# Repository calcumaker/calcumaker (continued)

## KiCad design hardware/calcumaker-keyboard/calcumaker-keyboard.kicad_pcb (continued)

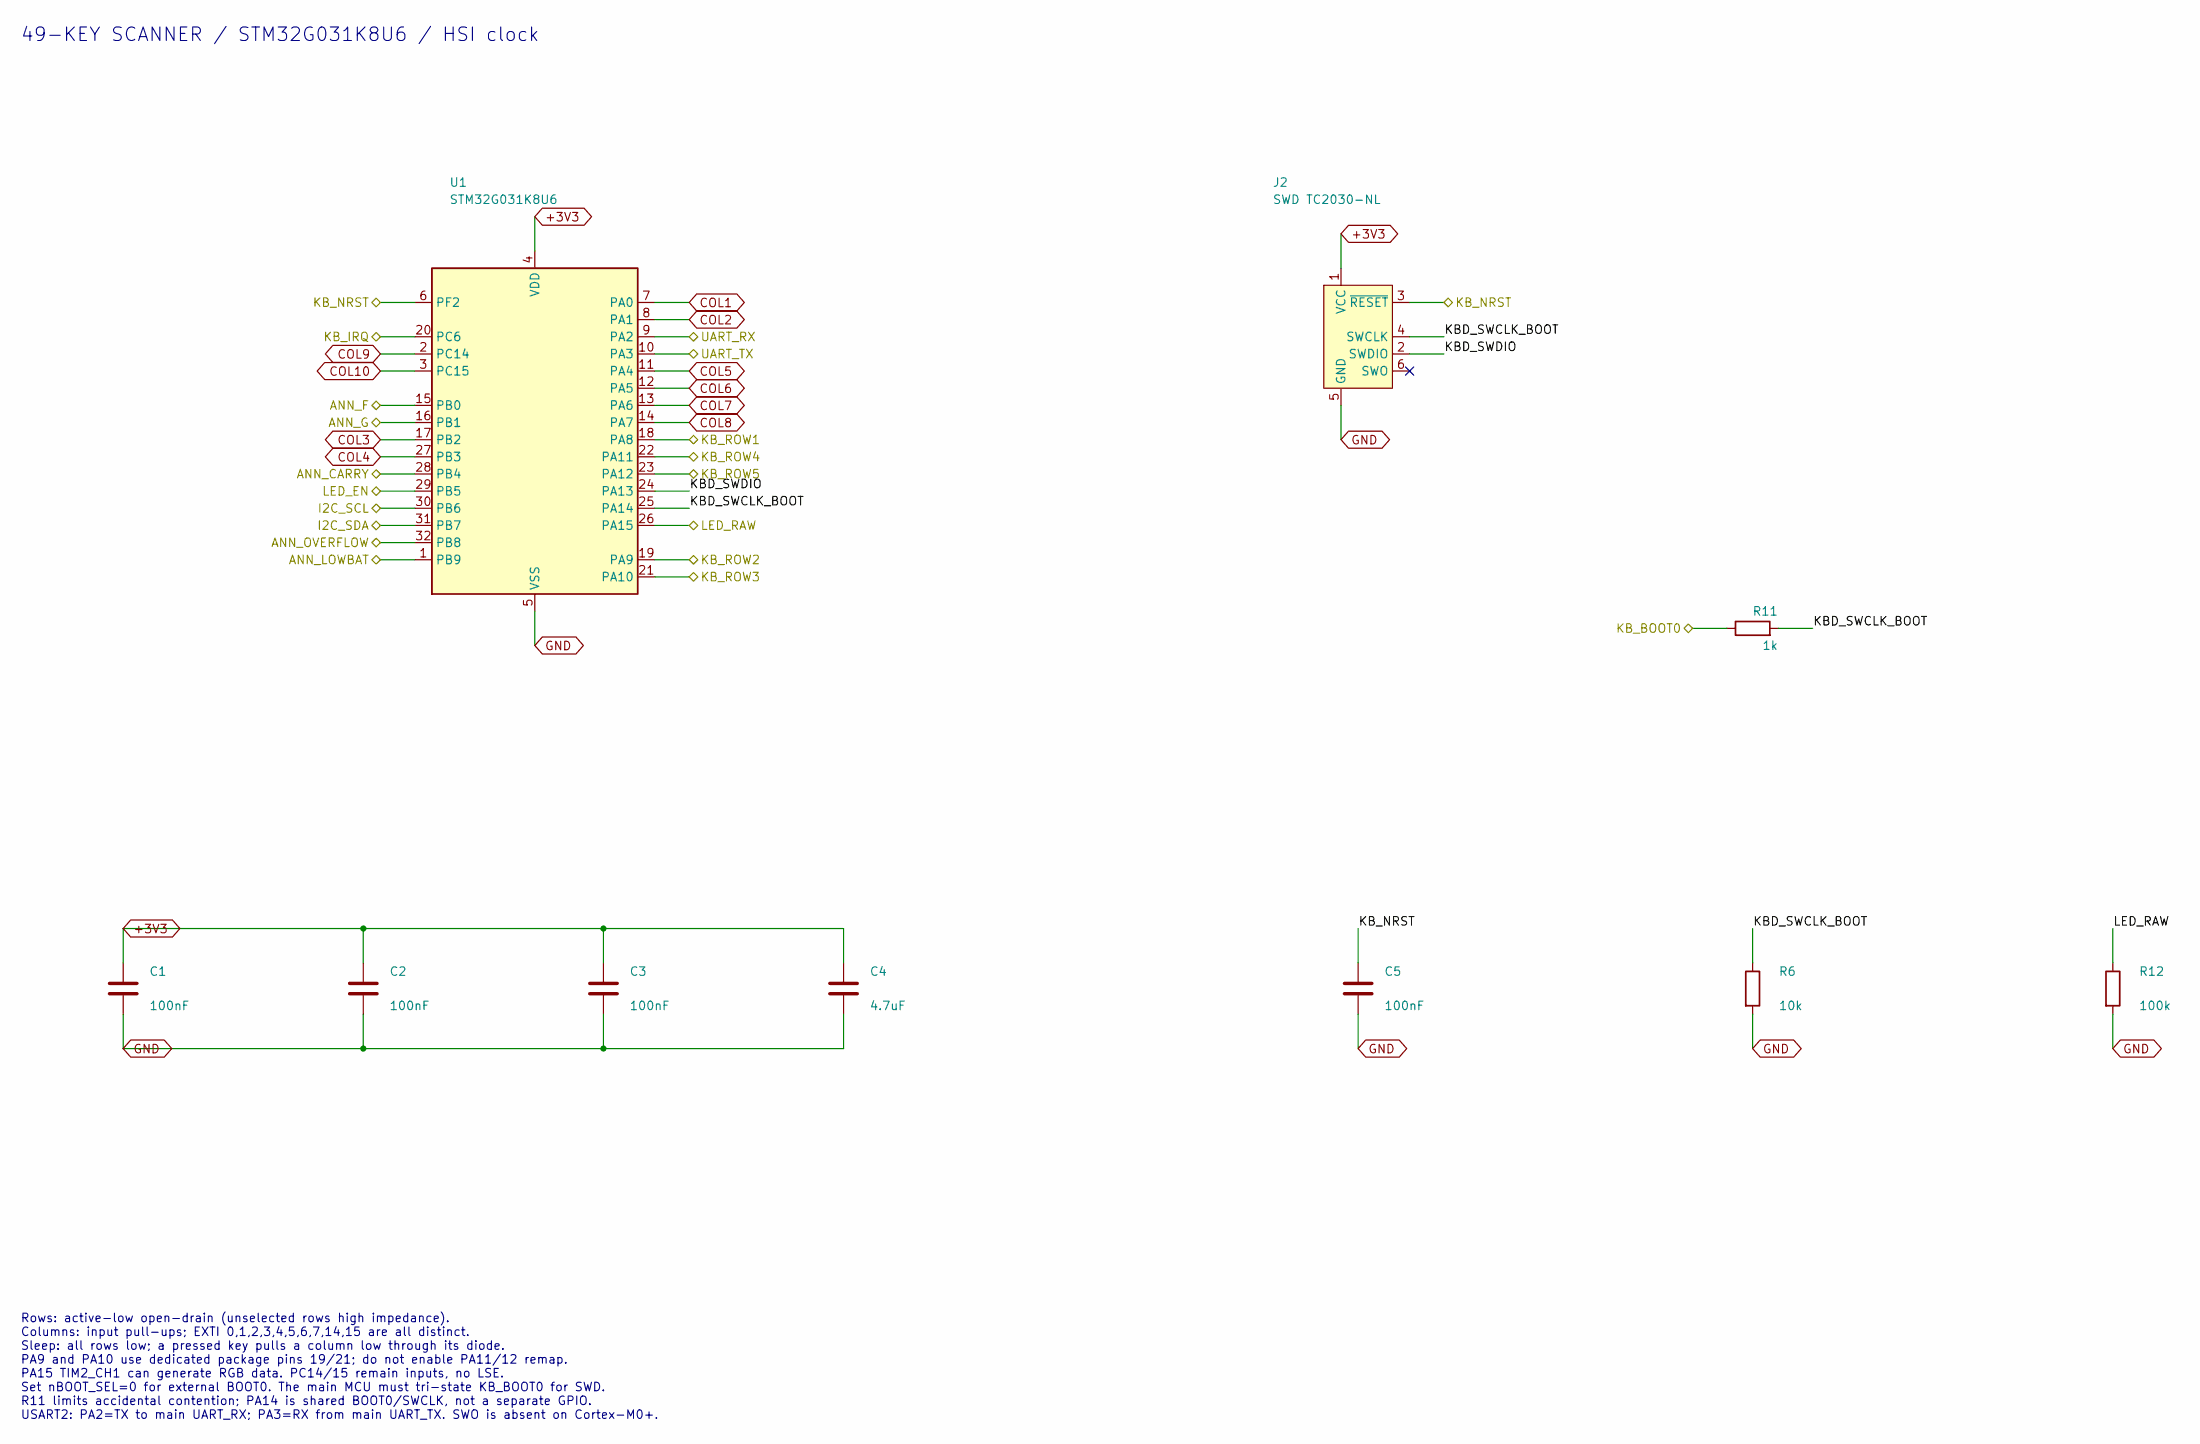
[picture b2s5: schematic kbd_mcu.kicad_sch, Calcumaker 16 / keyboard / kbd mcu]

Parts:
C1, C2, C3, C5: 100nF; C_0402_1005Metric; LCSC C1525
C4: 4.7uF; C_0603_1608Metric
J2: SWD TC2030-NL; Tag-Connect_TC2030-IDC-NL_2x03_P1.27mm_Vertical
R6: 10k; R_0402_1005Metric; LCSC C25744
R11: 1k; R_0402_1005Metric
R12: 100k; R_0402_1005Metric
U1: STM32G031K8U6; UFQFPN-32-1EP_5x5mm_P0.5mm_EP3.5x3.5mm; MPN STM32G031K8U6; LCSC C432207

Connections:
+3V3: C1.1, C2.1, C3.1, C4.1, J2.1 (VCC), U1.4 (VDD); also elsewhere on the board
/ANN_CARRY: U1.28 (PB4); also elsewhere on the board
/ANN_F: U1.15 (PB0); also elsewhere on the board
/ANN_G: U1.16 (PB1); also elsewhere on the board
/ANN_LOWBAT: U1.1 (PB9); also elsewhere on the board
/ANN_OVERFLOW: U1.32 (PB8); also elsewhere on the board
/I2C_SCL: U1.30 (PB6); also elsewhere on the board
/I2C_SDA: U1.31 (PB7); also elsewhere on the board
/KB_BOOT0: R11.1; also elsewhere on the board
/KB_IRQ: U1.20 (PC6); also elsewhere on the board
/KB_NRST: C5.1, J2.3 (~RESET), U1.6 (PF2); also elsewhere on the board
/KB_ROW1: U1.18 (PA8); also elsewhere on the board
/KB_ROW2: U1.19 (PA9); also elsewhere on the board
/KB_ROW3: U1.21 (PA10); also elsewhere on the board
/KB_ROW4: U1.22 (PA11); also elsewhere on the board
/KB_ROW5: U1.23 (PA12); also elsewhere on the board
/KbdMCU/KBD_SWCLK_BOOT: J2.4 (SWCLK), R6.1, R11.2, U1.25 (PA14)
/KbdMCU/KBD_SWDIO: J2.2 (SWDIO), U1.24 (PA13)
/LED_EN: U1.29 (PB5); also elsewhere on the board
/LED_RAW: R12.1, U1.26 (PA15); also elsewhere on the board
/UART_RX: U1.9 (PA2); also elsewhere on the board
/UART_TX: U1.10 (PA3); also elsewhere on the board
COL1: U1.7 (PA0); also elsewhere on the board
COL2: U1.8 (PA1); also elsewhere on the board
COL3: U1.17 (PB2); also elsewhere on the board
COL4: U1.27 (PB3); also elsewhere on the board
COL5: U1.11 (PA4); also elsewhere on the board
COL6: U1.12 (PA5); also elsewhere on the board
COL7: U1.13 (PA6); also elsewhere on the board
COL8: U1.14 (PA7); also elsewhere on the board
COL9: U1.2 (PC14); also elsewhere on the board
COL10: U1.3 (PC15); also elsewhere on the board
GND: C1.2, C2.2, C3.2, C4.2, C5.2, J2.5 (GND), R6.2, R12.2, U1.5 (VSS), U1.33 (VSS); also elsewhere on the board

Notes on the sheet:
49-KEY SCANNER / STM32G031K8U6 / HSI clock
Rows: active-low open-drain (unselected rows high impedance). Columns: input pull-ups; EXTI 0,1,2,3,4,5,6,7,14,15 are all distinct. Sleep: all rows low; a pressed key pulls a column low through its diode. PA9 and PA10 use dedicated package pins 19/21; do not enable PA11/12 remap. PA15 TIM2_CH1 can 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

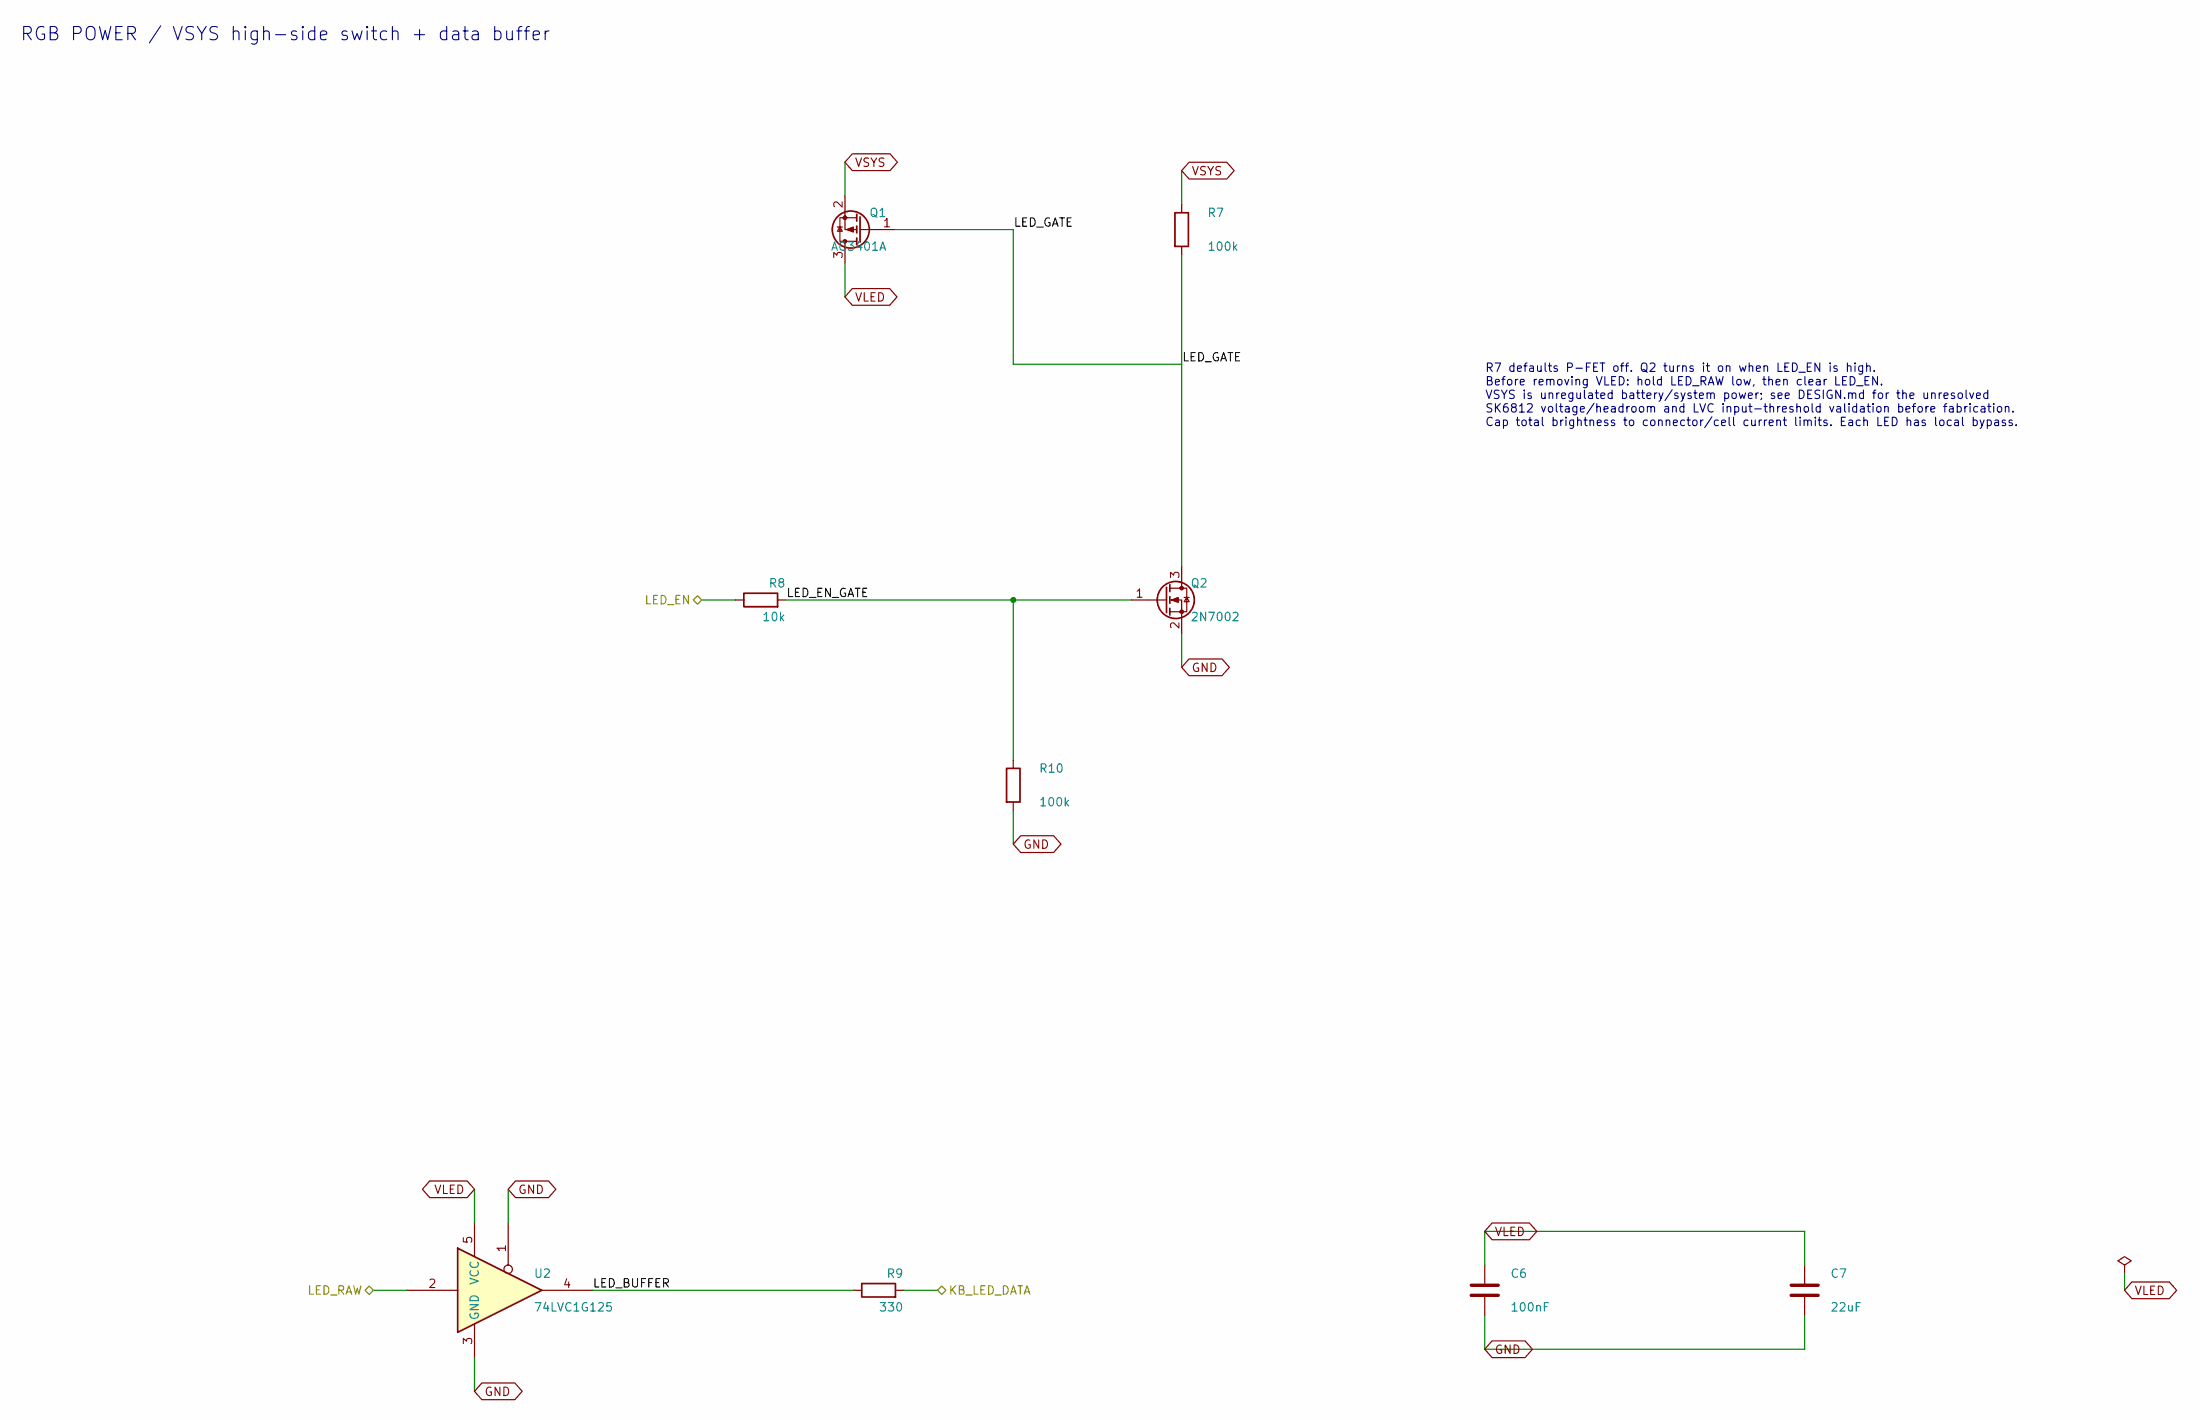
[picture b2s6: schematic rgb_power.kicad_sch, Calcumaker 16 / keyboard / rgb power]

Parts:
C6: 100nF; C_0402_1005Metric; LCSC C1525
C7: 22uF; C_0603_1608Metric
Q1: AO3401A; SOT-23; MPN AO3401A; LCSC C15127
Q2: 2N7002; SOT-23; MPN 2N7002; LCSC C8545
R7, R10: 100k; R_0402_1005Metric; LCSC C25741
R8: 10k; R_0402_1005Metric; LCSC C25744
R9: 330; R_0402_1005Metric
U2: 74LVC1G125; SOT-23-5; MPN SN74LVC1G125DBVR; LCSC C23654

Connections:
/LED_EN: R8.1; also elsewhere on the board
/LED_RAW: U2.2; also elsewhere on the board
/RGBPower/LED_BUFFER: R9.1, U2.4
/RGBPower/LED_EN_GATE: Q2.1 (G), R8.2, R10.1
/RGBPower/LED_GATE: Q1.1 (G), Q2.3 (D), R7.2
/RGB_FIRST: R9.2; also elsewhere on the board
GND: C6.2, C7.2, Q2.2 (S), R10.2, U2.1, U2.3 (GND); also elsewhere on the board
VLED: C6.1, C7.1, Q1.3 (D), U2.5 (VCC); also elsewhere on the board
VSYS: Q1.2 (S), R7.1; also elsewhere on the board

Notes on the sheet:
RGB POWER / VSYS high-side switch + data buffer
R7 defaults P-FET off. Q2 turns it on when LED_EN is high. Before removing VLED: hold LED_RAW low, then clear LED_EN. VSYS is unregulated battery/system power; see DESIGN.md for the unresolved SK6812 voltage/headroom and LVC input-threshold validation before fabrication. Cap total brightness to con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

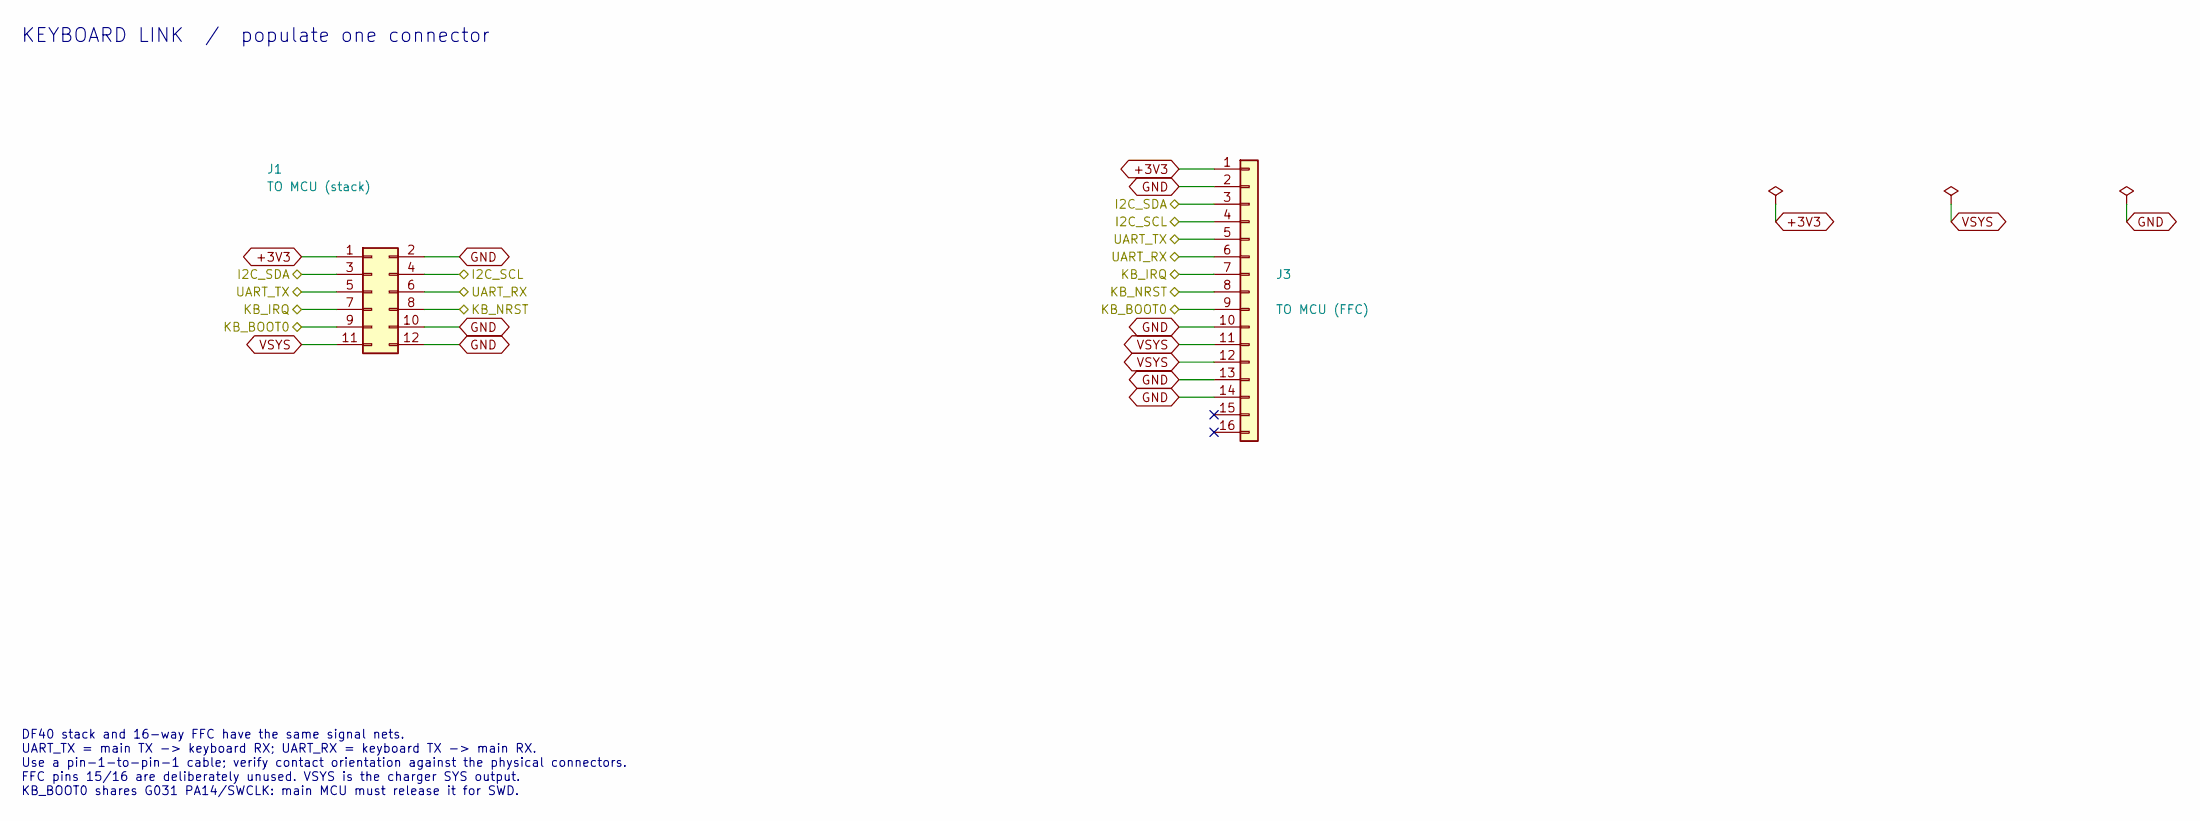
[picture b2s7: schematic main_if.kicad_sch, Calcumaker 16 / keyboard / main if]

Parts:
J1: TO MCU (stack); Hirose_DF40C-12DP-0.4V_2x06-1MP_P0.4mm; MPN DF40C-12DP-0.4V(51); LCSC C6224952
J3: TO MCU (FFC); Hirose_FH12-16S-0.5SH_1x16-1MP_P0.50mm_Horizontal; MPN AFC01-S16FCA-00; LCSC C262665

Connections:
+3V3: J1.1, J3.1; also elsewhere on the board
/I2C_SCL: J1.4, J3.4; also elsewhere on the board
/I2C_SDA: J1.3, J3.3; also elsewhere on the board
/KB_BOOT0: J1.9, J3.9; also elsewhere on the board
/KB_IRQ: J1.7, J3.7; also elsewhere on the board
/KB_NRST: J1.8, J3.8; also elsewhere on the board
/UART_RX: J1.6, J3.6; also elsewhere on the board
/UART_TX: J1.5, J3.5; also elsewhere on the board
GND: J1.2, J1.10, J1.12, J3.2, J3.10, J3.13, J3.14; also elsewhere on the board
VSYS: J1.11, J3.11, J3.12; also elsewhere on the board

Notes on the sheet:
KEYBOARD LINK / populate one connector
DF40 stack and 16-way FFC have the same signal nets. UART_TX = main TX -> keyboard RX; UART_RX = keyboard TX -> main RX. Use a pin-1-to-pin-1 cable; verify contact orientation against the physical connectors. FFC pins 15/16 are deliberately unused. VSYS is the charger SYS output. KB_BOOT0 shares G0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

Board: 2 copper layers, 227 parts (222 on the bottom side), 141 nets, no tracks yet.

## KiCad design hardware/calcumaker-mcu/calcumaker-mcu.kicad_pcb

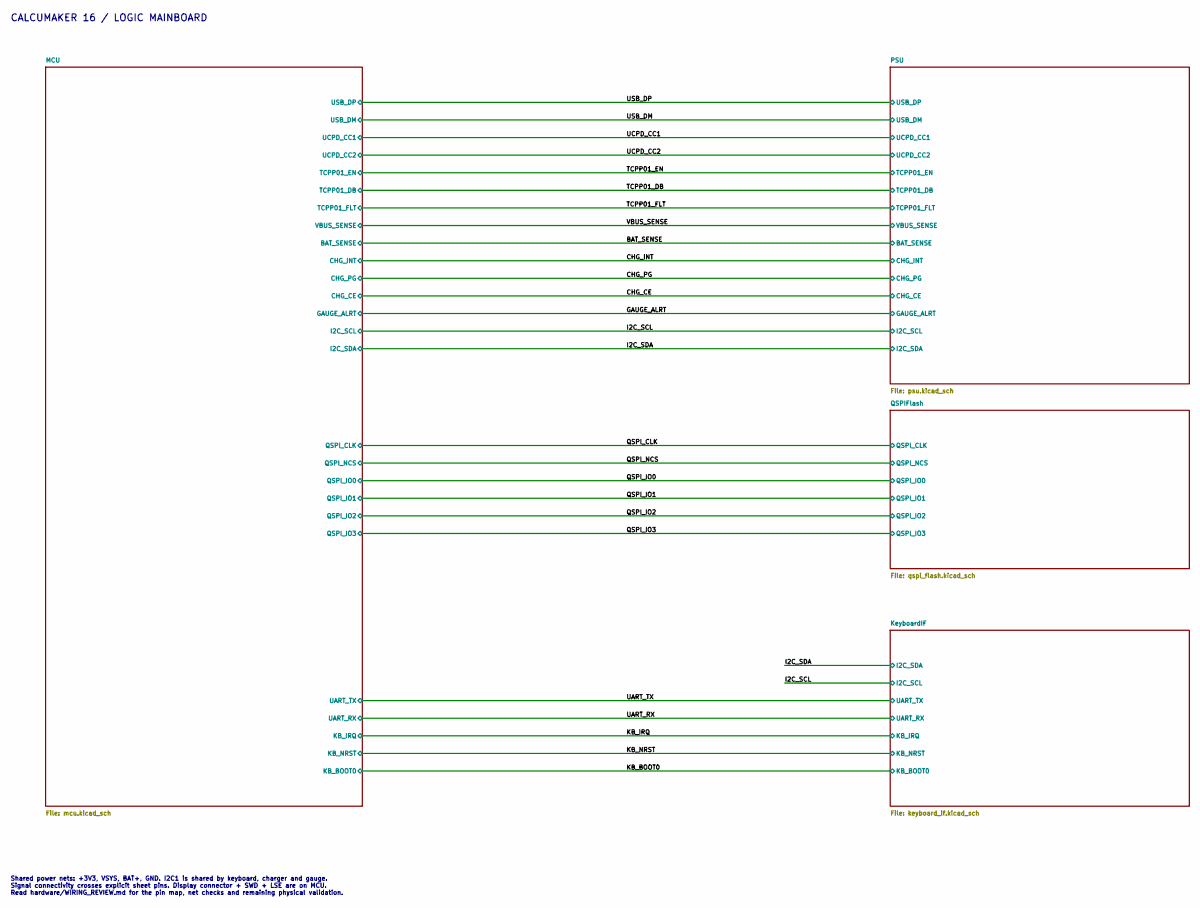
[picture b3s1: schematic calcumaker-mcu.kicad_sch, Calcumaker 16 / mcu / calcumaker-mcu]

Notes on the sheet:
CALCUMAKER 16 / LOGIC MAINBOARD
Shared power nets: +3V3, VSYS, BAT+, GND. I2C1 is shared by keyboard, charger and gauge. Signal connectivity crosses explicit sheet pins. Display connector + SWD + LSE are on MCU. Read hardware/WIRING_REVIEW.md for the pin map, net checks and remaining physical validation.

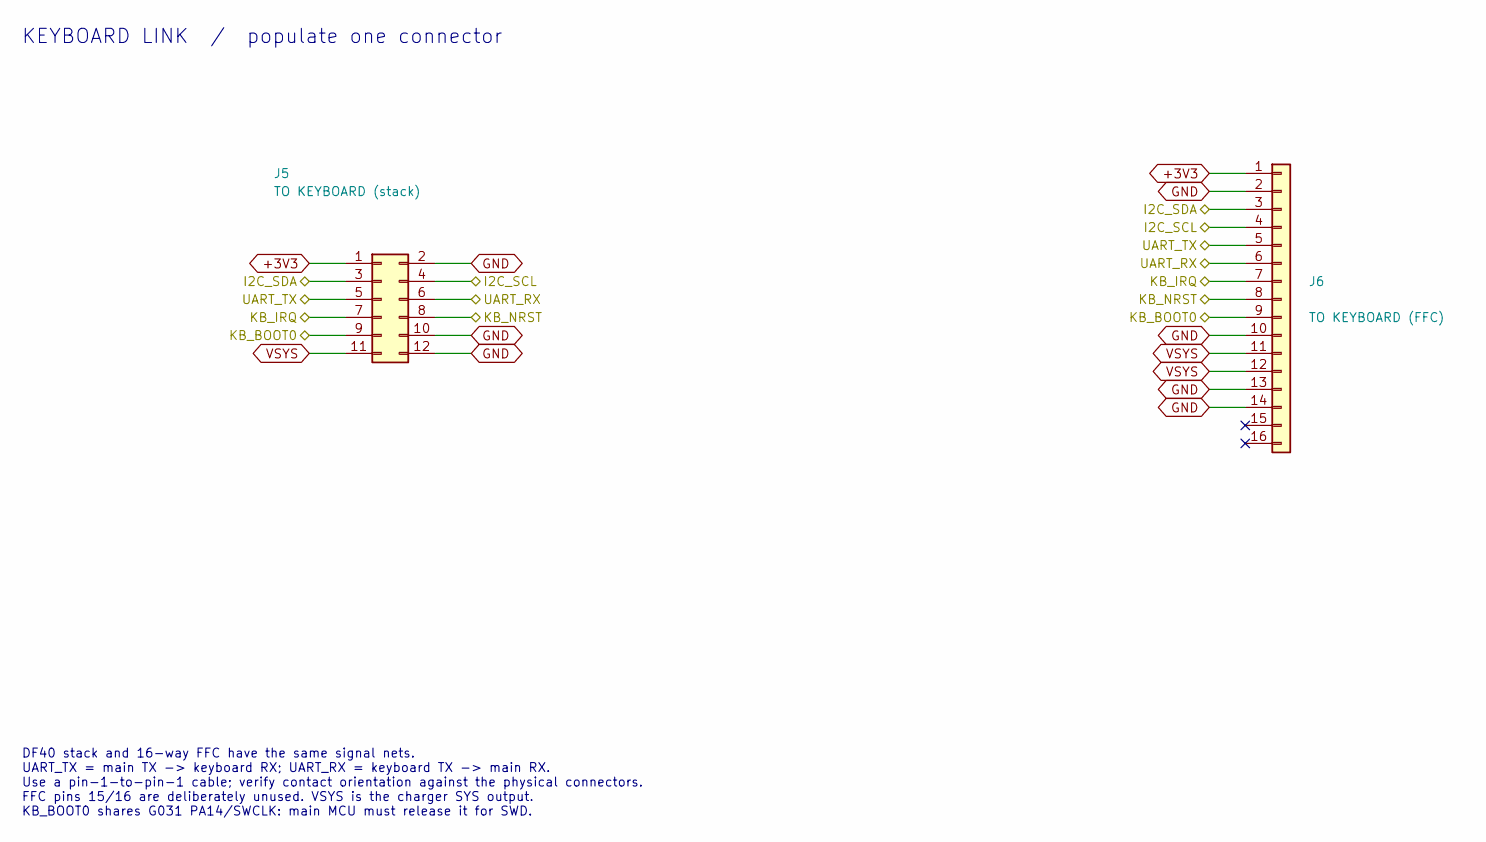
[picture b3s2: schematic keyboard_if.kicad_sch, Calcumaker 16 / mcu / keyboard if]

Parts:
J5: TO KEYBOARD (stack); Hirose_DF40B-12DS-0.4V_2x06-1MP_P0.4mm; MPN DF40B-12DS-0.4V(58); LCSC C3641147
J6: TO KEYBOARD (FFC); Hirose_FH12-16S-0.5SH_1x16-1MP_P0.50mm_Horizontal; MPN AFC01-S16FCA-00; LCSC C262665

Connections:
+3V3: J5.1, J6.1; also elsewhere on the board
/I2C_SCL: J5.4, J6.4; also elsewhere on the board
/I2C_SDA: J5.3, J6.3; also elsewhere on the board
/KB_BOOT0: J5.9, J6.9; also elsewhere on the board
/KB_IRQ: J5.7, J6.7; also elsewhere on the board
/KB_NRST: J5.8, J6.8; also elsewhere on the board
/UART_RX: J5.6, J6.6; also elsewhere on the board
/UART_TX: J5.5, J6.5; also elsewhere on the board
GND: J5.2, J5.10, J5.12, J6.2, J6.10, J6.13, J6.14; also elsewhere on the board
VSYS: J5.11, J6.11, J6.12; also elsewhere on the board

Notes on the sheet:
KEYBOARD LINK / populate one connector
DF40 stack and 16-way FFC have the same signal nets. UART_TX = main TX -> keyboard RX; UART_RX = keyboard TX -> main RX. Use a pin-1-to-pin-1 cable; verify contact orientation against the physical connectors. FFC pins 15/16 are deliberately unused. VSYS is the charger SYS output. KB_BOOT0 shares G0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

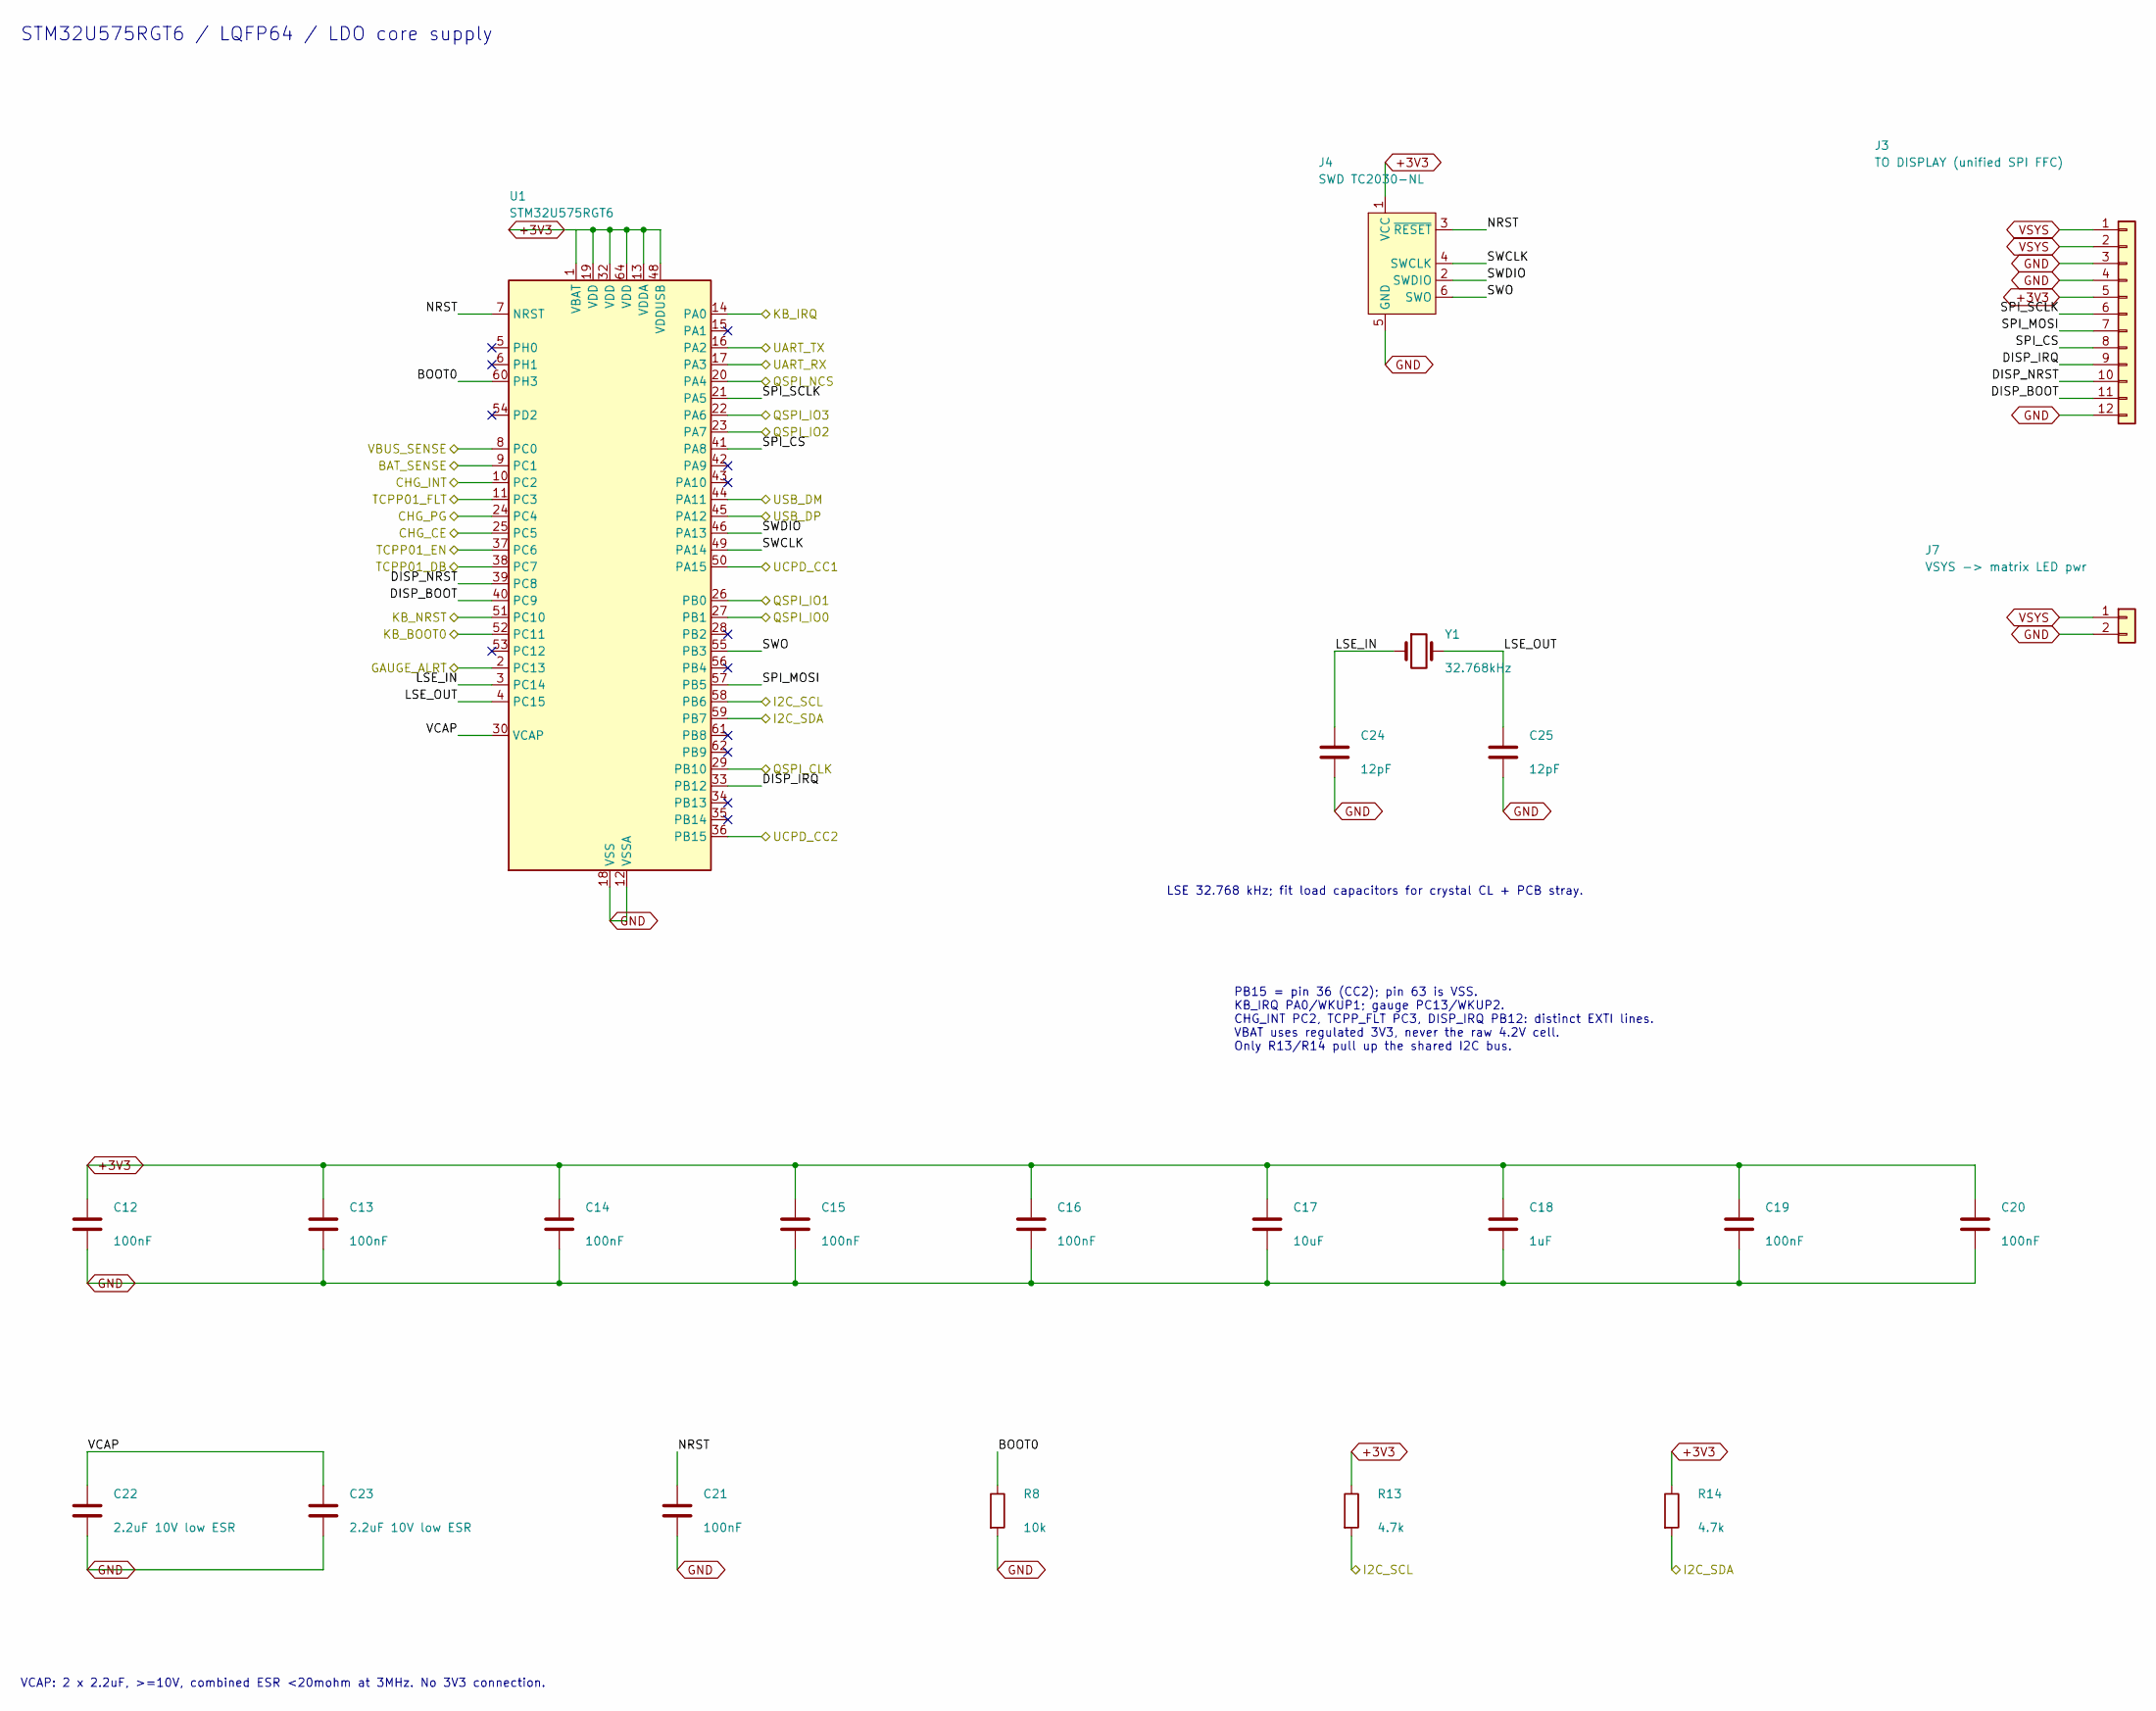
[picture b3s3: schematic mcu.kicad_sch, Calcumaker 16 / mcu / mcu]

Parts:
C12, C13, C14, C15, C16, C19, C20, C21: 100nF; C_0402_1005Metric; LCSC C1525
C17: 10uF; C_0603_1608Metric
C18: 1uF; C_0402_1005Metric; LCSC C29266
C22, C23: 2.2uF 10V low ESR; C_0603_1608Metric
C24, C25: 12pF; C_0402_1005Metric; LCSC C1547
J3: TO DISPLAY (unified SPI FFC); Hirose_FH12-12S-0.5SH_1x12-1MP_P0.50mm_Horizontal; MPN AFC01-S12FCA-00; LCSC C262661
J4: SWD TC2030-NL; Tag-Connect_TC2030-IDC-NL_2x03_P1.27mm_Vertical
J7: VSYS -> matrix LED pwr; JST_PH_S2B-PH-K_1x02_P2.00mm_Horizontal; MPN S2B-PH-K-S; LCSC C173752
R8: 10k; R_0402_1005Metric; LCSC C25744
R13, R14: 4.7k; R_0402_1005Metric
U1: STM32U575RGT6; LQFP-64_10x10mm_P0.5mm; MPN STM32U575RGT6; LCSC C5270980
Y1: 32.768kHz; Crystal_SMD_3215-2Pin_3.2x1.5mm; MPN Q13FC13500004; LCSC C32346

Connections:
+3V3: C12.1, C13.1, C14.1, C15.1, C16.1, C17.1, C18.1, C19.1, C20.1, J3.5, J4.1 (VCC), R13.1, R14.1, U1.1 (VBAT), U1.13 (VDDA), U1.19 (VDD), U1.32 (VDD), U1.48 (VDDUSB), U1.64 (VDD); also elsewhere on the board
/BAT_SENSE: U1.9 (PC1); also elsewhere on the board
/CHG_CE: U1.25 (PC5); also elsewhere on the board
/CHG_INT: U1.10 (PC2); also elsewhere on the board
/CHG_PG: U1.24 (PC4); also elsewhere on the board
/GAUGE_ALRT: U1.2 (PC13); also elsewhere on the board
/I2C_SCL: R13.2, U1.58 (PB6); also elsewhere on the board
/I2C_SDA: R14.2, U1.59 (PB7); also elsewhere on the board
/KB_BOOT0: U1.52 (PC11); also elsewhere on the board
/KB_IRQ: U1.14 (PA0); also elsewhere on the board
/KB_NRST: U1.51 (PC10); also elsewhere on the board
/MCU/BOOT0: R8.1, U1.60 (PH3)
/MCU/DISP_BOOT: J3.11, U1.40 (PC9)
/MCU/DISP_IRQ: J3.9, U1.33 (PB12)
/MCU/DISP_NRST: J3.10, U1.39 (PC8)
/MCU/LSE_IN: C24.1, U1.3 (PC14), Y1.1
/MCU/LSE_OUT: C25.1, U1.4 (PC15), Y1.2
/MCU/NRST: C21.1, J4.3 (~RESET), U1.7 (NRST)
/MCU/SPI_CS: J3.8, U1.41 (PA8)
/MCU/SPI_MOSI: J3.7, U1.57 (PB5)
/MCU/SPI_SCLK: J3.6, U1.21 (PA5)
/MCU/SWCLK: J4.4 (SWCLK), U1.49 (PA14)
/MCU/SWDIO: J4.2 (SWDIO), U1.46 (PA13)
/MCU/SWO: J4.6 (SWO), U1.55 (PB3)
/MCU/VCAP: C22.1, C23.1, U1.30 (VCAP)
/QSPI_CLK: U1.29 (PB10); also elsewhere on the board
/QSPI_IO0: U1.27 (PB1); also elsewhere on the board
/QSPI_IO1: U1.26 (PB0); also elsewhere on the board
/QSPI_IO2: U1.23 (PA7); also elsewhere on the board
/QSPI_IO3: U1.22 (PA6); also elsewhere on the board
/QSPI_NCS: U1.20 (PA4); also elsewhere on the board
/TCPP01_DB: U1.38 (PC7); also elsewhere on the board
/TCPP01_EN: U1.37 (PC6); also elsewhere on the board
/TCPP01_FLT: U1.11 (PC3); also elsewhere on the board
/UART_RX: U1.17 (PA3); also elsewhere on the board
/UART_TX: U1.16 (PA2); also elsewhere on the board
/UCPD_CC1: U1.50 (PA15); also elsewhere on the board
/UCPD_CC2: U1.36 (PB15); also elsewhere on the board
/USB_DM: U1.44 (PA11); also elsewhere on the board
/USB_DP: U1.45 (PA12); also elsewhere on the board
/VBUS_SENSE: U1.8 (PC0); also elsewhere on the board
GND: C12.2, C13.2, C14.2, C15.2, C16.2, C17.2, C18.2, C19.2, C20.2, C21.2, C22.2, C23.2, C24.2, C25.2, J3.3, J3.4, J3.12, J4.5 (GND), J7.2, R8.2, U1.12 (VSSA), U1.18 (VSS), U1.31 (VSS), U1.47 (VSS), U1.63 (VSS); also elsewhere on the board
VSYS: J3.1, J3.2, J7.1; also elsewhere on the board

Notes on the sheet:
PB15 = pin 36 (CC2); pin 63 is VSS. KB_IRQ PA0/WKUP1; gauge PC13/WKUP2. CHG_INT PC2, TCPP_FLT PC3, DISP_IRQ PB12: distinct EXTI lines. VBAT uses regulated 3V3, never the raw 4.2V cell. Only R13/R14 pull up the shared I2C bus.
STM32U575RGT6 / LQFP64 / LDO core supply
LSE 32.768 kHz; fit load capacitors for crystal CL + PCB stray.
VCAP: 2 x 2.2uF, >=10V, combined ESR <20mohm at 3MHz. No 3V3 connection.

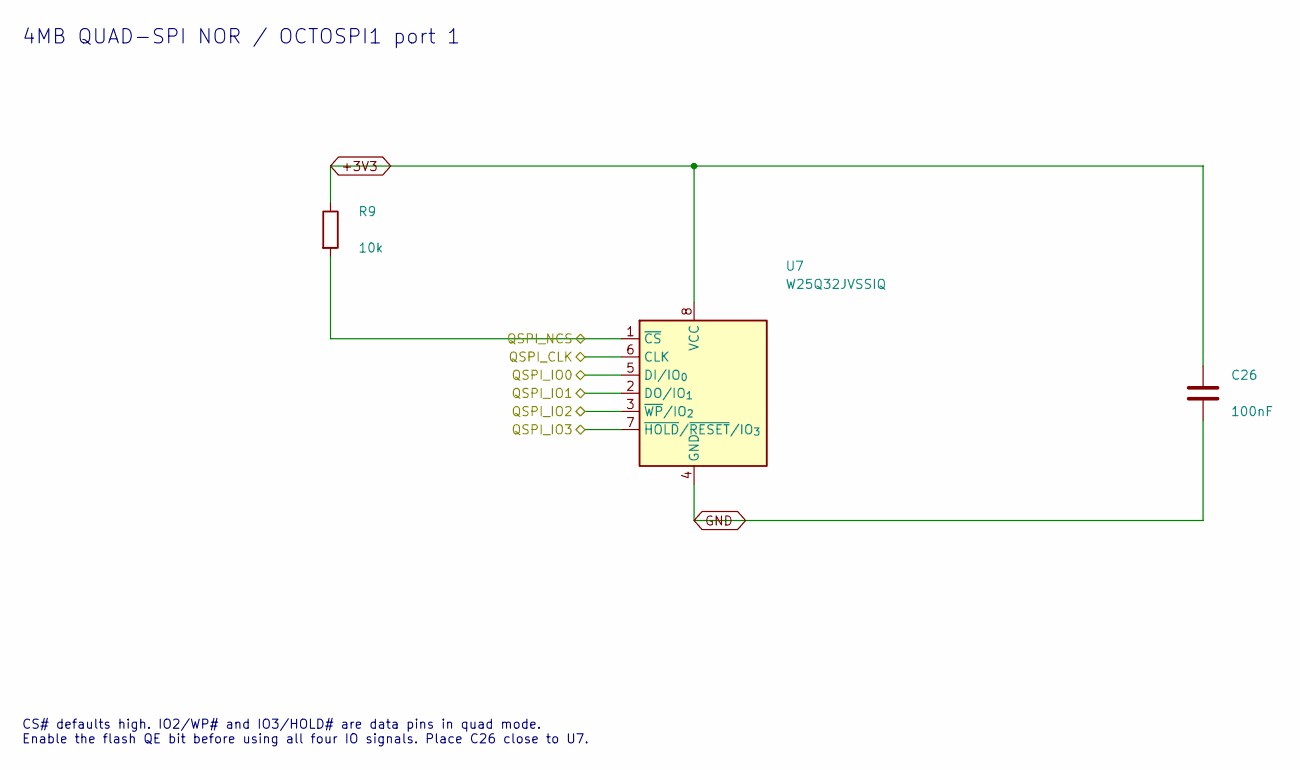
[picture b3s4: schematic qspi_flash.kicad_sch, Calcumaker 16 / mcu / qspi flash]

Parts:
C26: 100nF; C_0402_1005Metric; LCSC C1525
R9: 10k; R_0402_1005Metric; LCSC C25744
U7: W25Q32JVSSIQ; SOIC-8_5.3x5.3mm_P1.27mm; MPN W25Q32JVSSIQ; LCSC C179173

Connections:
+3V3: C26.1, R9.1, U7.8 (VCC); also elsewhere on the board
/QSPI_CLK: U7.6 (CLK); also elsewhere on the board
/QSPI_IO0: U7.5 (DI/IO_{0}); also elsewhere on the board
/QSPI_IO1: U7.2 (DO/IO_{1}); also elsewhere on the board
/QSPI_IO2: U7.3 (~WP/IO_{2}); also elsewhere on the board
/QSPI_IO3: U7.7 (~HOLD/~RESET/IO_{3}); also elsewhere on the board
/QSPI_NCS: R9.2, U7.1 (~CS); also elsewhere on the board
GND: C26.2, U7.4 (GND); also elsewhere on the board

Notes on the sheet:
4MB QUAD-SPI NOR / OCTOSPI1 port 1
CS# defaults high. IO2/WP# and IO3/HOLD# are data pins in quad mode. Enable the flash QE bit before using all four IO signals. Place C26 close to U7.
